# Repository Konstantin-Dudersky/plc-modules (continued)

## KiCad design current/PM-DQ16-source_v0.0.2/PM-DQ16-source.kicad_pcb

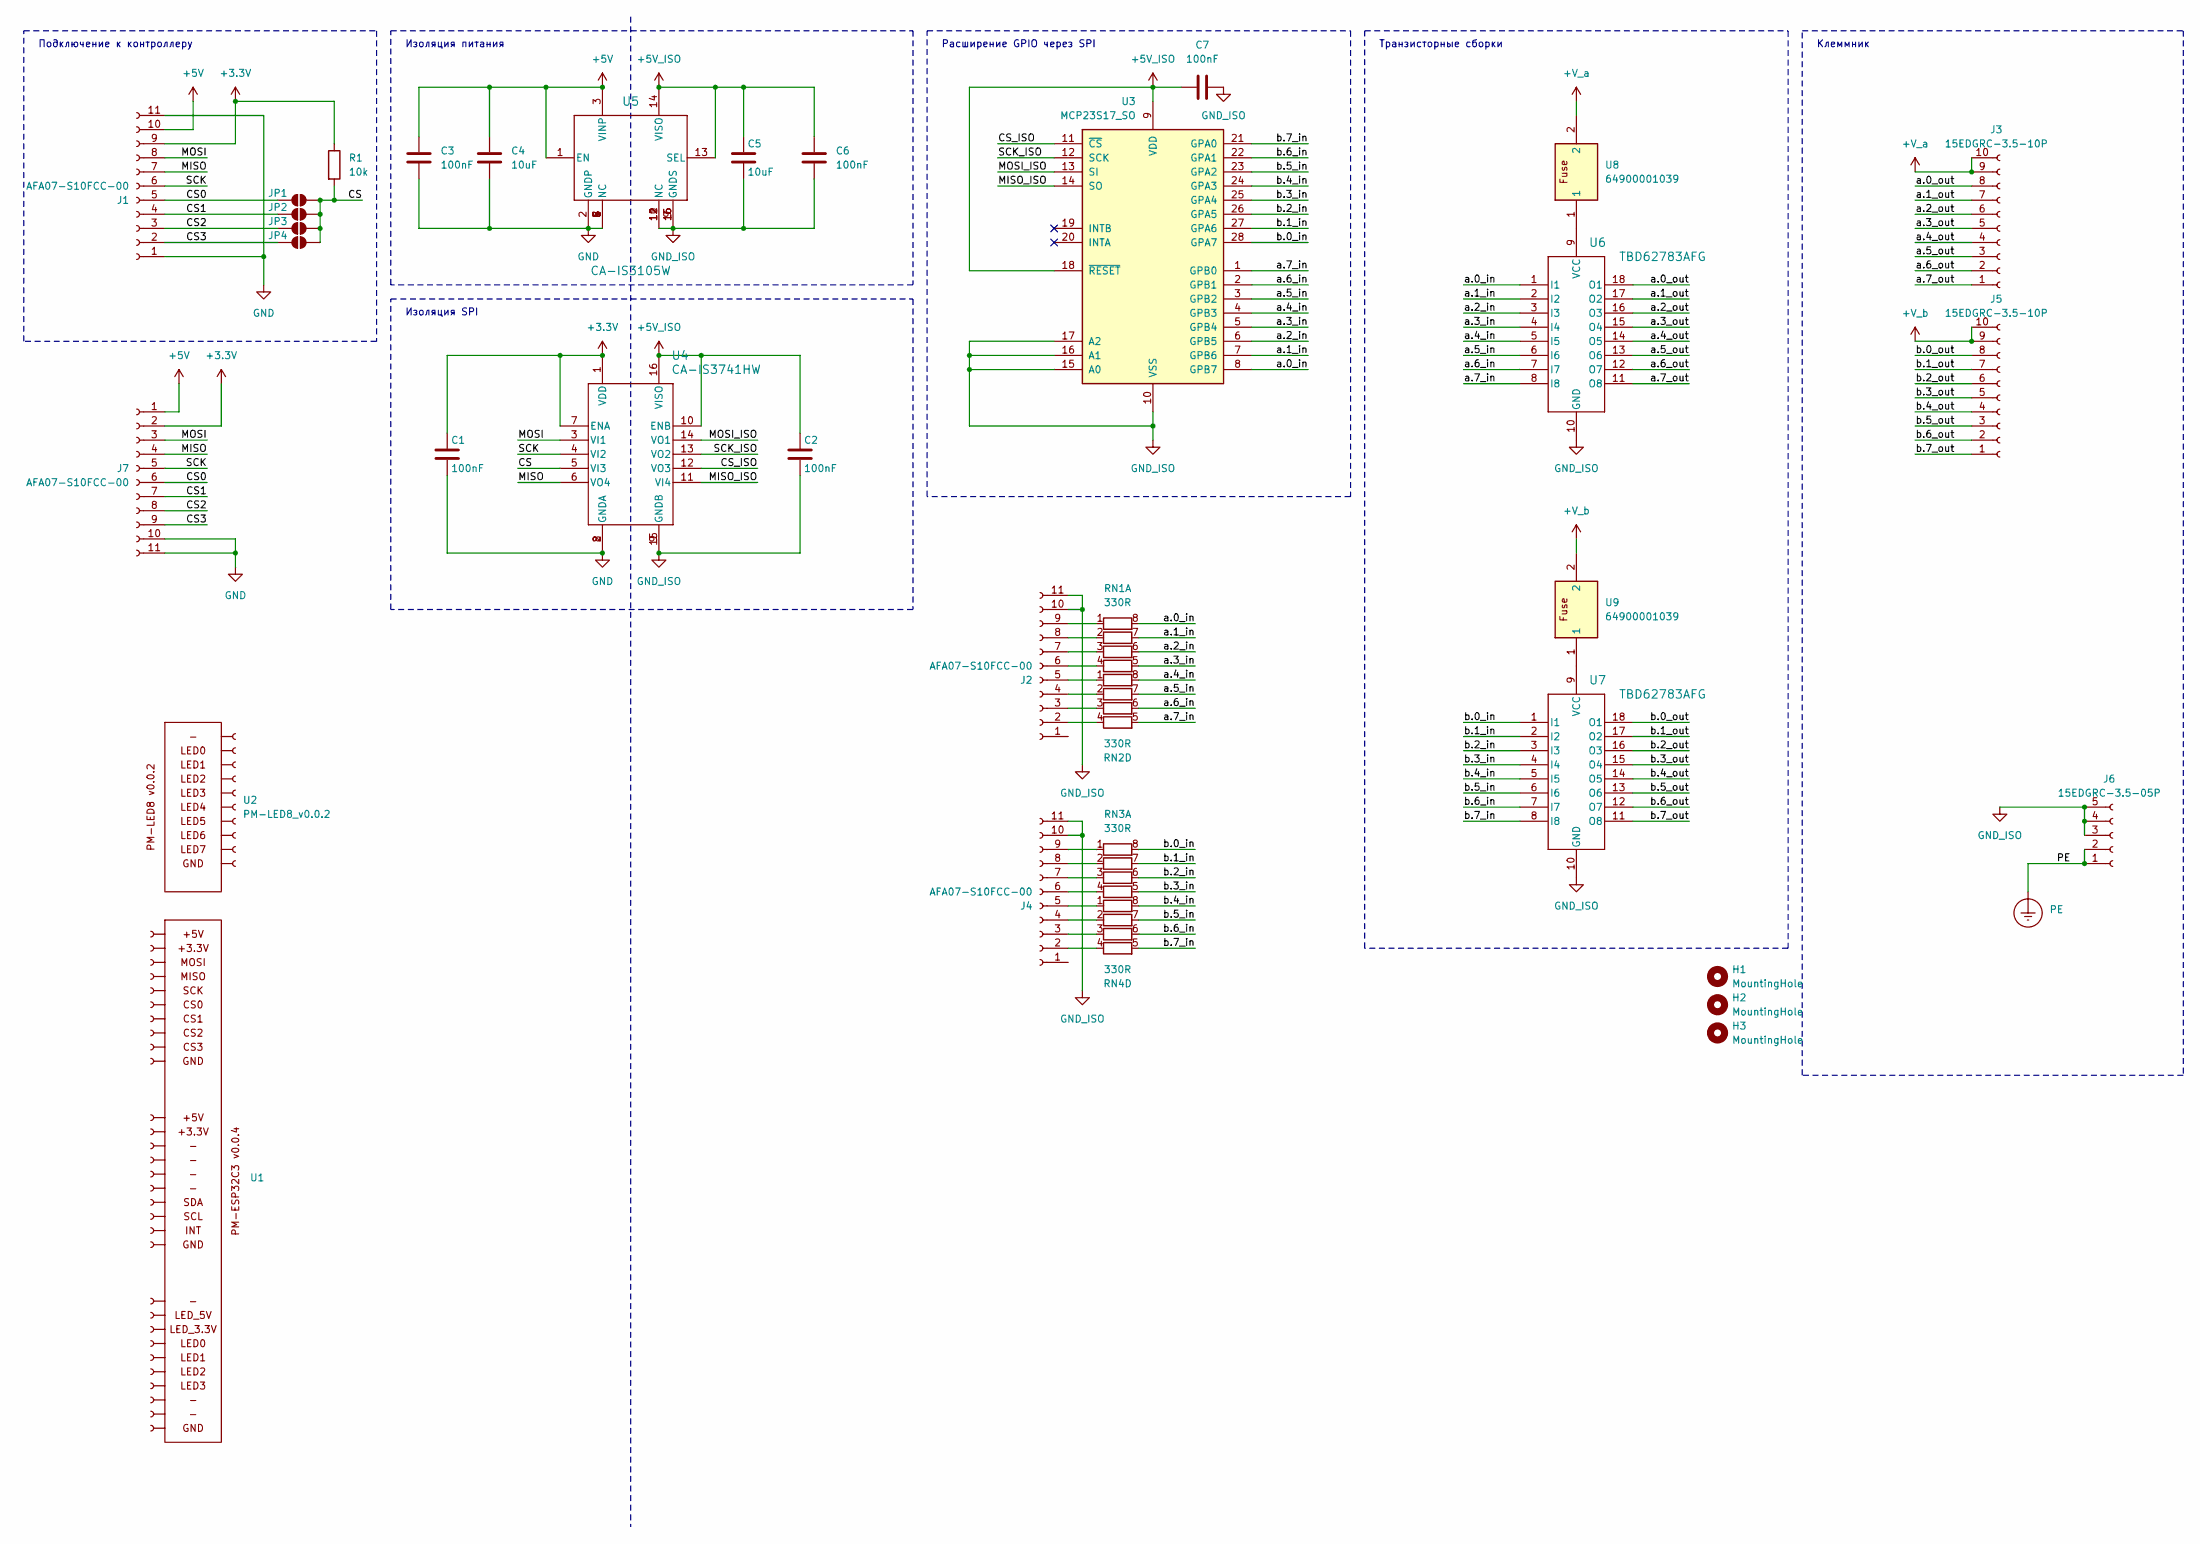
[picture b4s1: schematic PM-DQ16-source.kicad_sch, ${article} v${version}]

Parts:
C1, C2, C3, C6, C7: 100nF; C_0603_1608Metric; part_ipn C_100nF_16V_0603_MLCC-X7R
C4, C5: 10uF; C_0603_1608Metric; part_ipn C_10uF_16V_0603_MLCC-X5R
H1, H2, H3: MountingHole; MountingHole_3.2mm_M3
J1, J2, J4, J7: AFA07-S10FCC-00; CONN10_AFA07-S10_JUS; part_ipn AFA07-S10FCC-00
J3, J5: 15EDGRC-3.5-10P; part_ipn 15EDGRC-3.5-10P
J6: 15EDGRC-3.5-05P; part_ipn 15EDGRC-3.5-05P
JP1, JP2, JP3, JP4: SolderJumper_2_Open; SolderJumper-2_P1.3mm_Open_RoundedPad1.0x1.5mm
PE1: PE
R1: 10k; R_0603_1608Metric; part_ipn R_10k_0603_1%
RN1, RN2, RN3, RN4: 330R; R_Array_Convex_4x0603; part_ipn R_330R_0603x4_1%
U1: PM-ESP32C3_v0.0.4; part_ipn PM-ESP32C3_v0.0.4
U2: PM-LED8_v0.0.2; PM-LED_v0.0.2; part_ipn PM-LED8_v0.0.1
U3: MCP23S17_SO; SOIC-28W_7.5x17.9mm_P1.27mm; part_ipn MCP23S17-E/SO
U4: CA-IS3741HW; SOIC16-WBW_CLG-M; part_ipn CA-IS3741HW
U5: CA-IS3105W; SOIC16-WBW_CLG-M; part_ipn CA-IS3105W
U6, U7: TBD62783AFG; SOP18-P-375-1p27_TOS-M; part_ipn TBD62783AFG
U8, U9: 64900001039; Fuseholder; Manufacturer_Part_Number 64900001039; Mouser Part Number 576-64900001039

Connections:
+3.3V: C1.1, J1.9, J7.2, R1.1, U4.1 (VDD), U4.7 (ENA)
+5V: C3.1, C4.1, J1.10, J7.1, U5.1 (EN), U5.3 (VINP)
+5V_ISO: C2.1, C5.1, C6.1, C7.1, U3.9 (VDD), U3.18 (~RESET), U4.10 (ENB), U4.16 (VISO), U5.13 (SEL), U5.14 (VISO)
+V_a: J3.9, J3.10, U8.2
+V_b: J5.9, J5.10, U9.2
/CS: JP1.2 (B), JP2.2 (B), JP3.2 (B), JP4.2 (B), R1.2, U4.5 (VI3)
/CS0: J1.5, J7.6, JP1.1 (A)
/CS1: J1.4, J7.7, JP2.1 (A)
/CS2: J1.3, J7.8, JP3.1 (A)
/CS3: J1.2, J7.9, JP4.1 (A)
/CS_ISO: U3.11 (~CS), U4.12 (VO3)
/MISO: J1.7, J7.4, U4.6 (VO4)
/MISO_ISO: U3.14 (SO), U4.11 (VI4)
/MOSI: J1.8, J7.3, U4.3 (VI1)
/MOSI_ISO: U3.13 (SI), U4.14 (VO1)
/PE: J6.1, J6.2, PE1.1
/SCK: J1.6, J7.5, U4.4 (VI2)
/SCK_ISO: U3.12 (SCK), U4.13 (VO2)
/a.0_in: RN1.8 (R1.2), U3.8 (GPB7), U6.1 (I1)
/a.0_out: J3.8, U6.18 (O1)
/a.1_in: RN1.7 (R2.2), U3.7 (GPB6), U6.2 (I2)
/a.1_out: J3.7, U6.17 (O2)
/a.2_in: RN1.6 (R3.2), U3.6 (GPB5), U6.3 (I3)
/a.2_out: J3.6, U6.16 (O3)
/a.3_in: RN1.5 (R4.2), U3.5 (GPB4), U6.4 (I4)
/a.3_out: J3.5, U6.15 (O4)
/a.4_in: RN2.8 (R1.2), U3.4 (GPB3), U6.5 (I5)
/a.4_out: J3.4, U6.14 (O5)
/a.5_in: RN2.7 (R2.2), U3.3 (GPB2), U6.6 (I6)
/a.5_out: J3.3, U6.13 (O6)
/a.6_in: RN2.6 (R3.2), U3.2 (GPB1), U6.7 (I7)
/a.6_out: J3.2, U6.12 (O7)
/a.7_in: RN2.5 (R4.2), U3.1 (GPB0), U6.8 (I8)
/a.7_out: J3.1, U6.11 (O8)
/b.0_in: RN3.8 (R1.2), U3.28 (GPA7), U7.1 (I1)
/b.0_out: J5.8, U7.18 (O1)
/b.1_in: RN3.7 (R2.2), U3.27 (GPA6), U7.2 (I2)
/b.1_out: J5.7, U7.17 (O2)
/b.2_in: RN3.6 (R3.2), U3.26 (GPA5), U7.3 (I3)
/b.2_out: J5.6, U7.16 (O3)
/b.3_in: RN3.5 (R4.2), U3.25 (GPA4), U7.4 (I4)
/b.3_out: J5.5, U7.15 (O4)
/b.4_in: RN4.8 (R1.2), U3.24 (GPA3), U7.5 (I5)
/b.4_out: J5.4, U7.14 (O5)
/b.5_in: RN4.7 (R2.2), U3.23 (GPA2), U7.6 (I6)
/b.5_out: J5.3, U7.13 (O6)
/b.6_in: RN4.6 (R3.2), U3.22 (GPA1), U7.7 (I7)
/b.6_out: J5.2, U7.12 (O7)
/b.7_in: RN4.5 (R4.2), U3.21 (GPA0), U7.8 (I8)
/b.7_out: J5.1, U7.11 (O8)
GND: C1.2, C3.2, C4.2, J1.1, J1.11, J7.10, J7.11, U4.2 (GNDA), U4.8 (GNDA), U5.2 (GNDP), U5.4 (NC), U5.5 (NC), U5.6 (NC), U5.7 (NC), U5.8 (NC)
GND_ISO: C2.2, C5.2, C6.2, C7.2, J2.10, J2.11, J4.10, J4.11, J6.3, J6.4, J6.5, U3.10 (VSS), U3.15 (A0), U3.16 (A1), U3.17 (A2), U4.9 (GNDB), U4.15 (GNDB), U5.9 (GNDS), U5.10 (NC), U5.11 (NC), U5.12 (NC), U5.15 (GNDS), U5.16 (GNDS), U6.10 (GND), U7.10 (GND)
unnamed: J2.2, RN2.4 (R4.1)
unnamed: J2.3, RN2.3 (R3.1)
unnamed: J2.4, RN2.2 (R2.1)
unnamed: J2.5, RN2.1 (R1.1)
unnamed: J2.6, RN1.4 (R4.1)
unnamed: J2.7, RN1.3 (R3.1)
unnamed: J2.8, RN1.2 (R2.1)
unnamed: J2.9, RN1.1 (R1.1)
unnamed: J4.2, RN4.4 (R4.1)
unnamed: J4.3, RN4.3 (R3.1)
unnamed: J4.4, RN4.2 (R2.1)
unnamed: J4.5, RN4.1 (R1.1)
unnamed: J4.6, RN3.4 (R4.1)
unnamed: J4.7, RN3.3 (R3.1)
unnamed: J4.8, RN3.2 (R2.1)
unnamed: J4.9, RN3.1 (R1.1)
unnamed: U6.9 (VCC), U8.1
unnamed: U7.9 (VCC), U9.1

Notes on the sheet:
Изоляция SPI
Расширение GPIO через SPI
Подключение к контроллеру
Транзисторные сборки
Клеммник
Изоляция питания

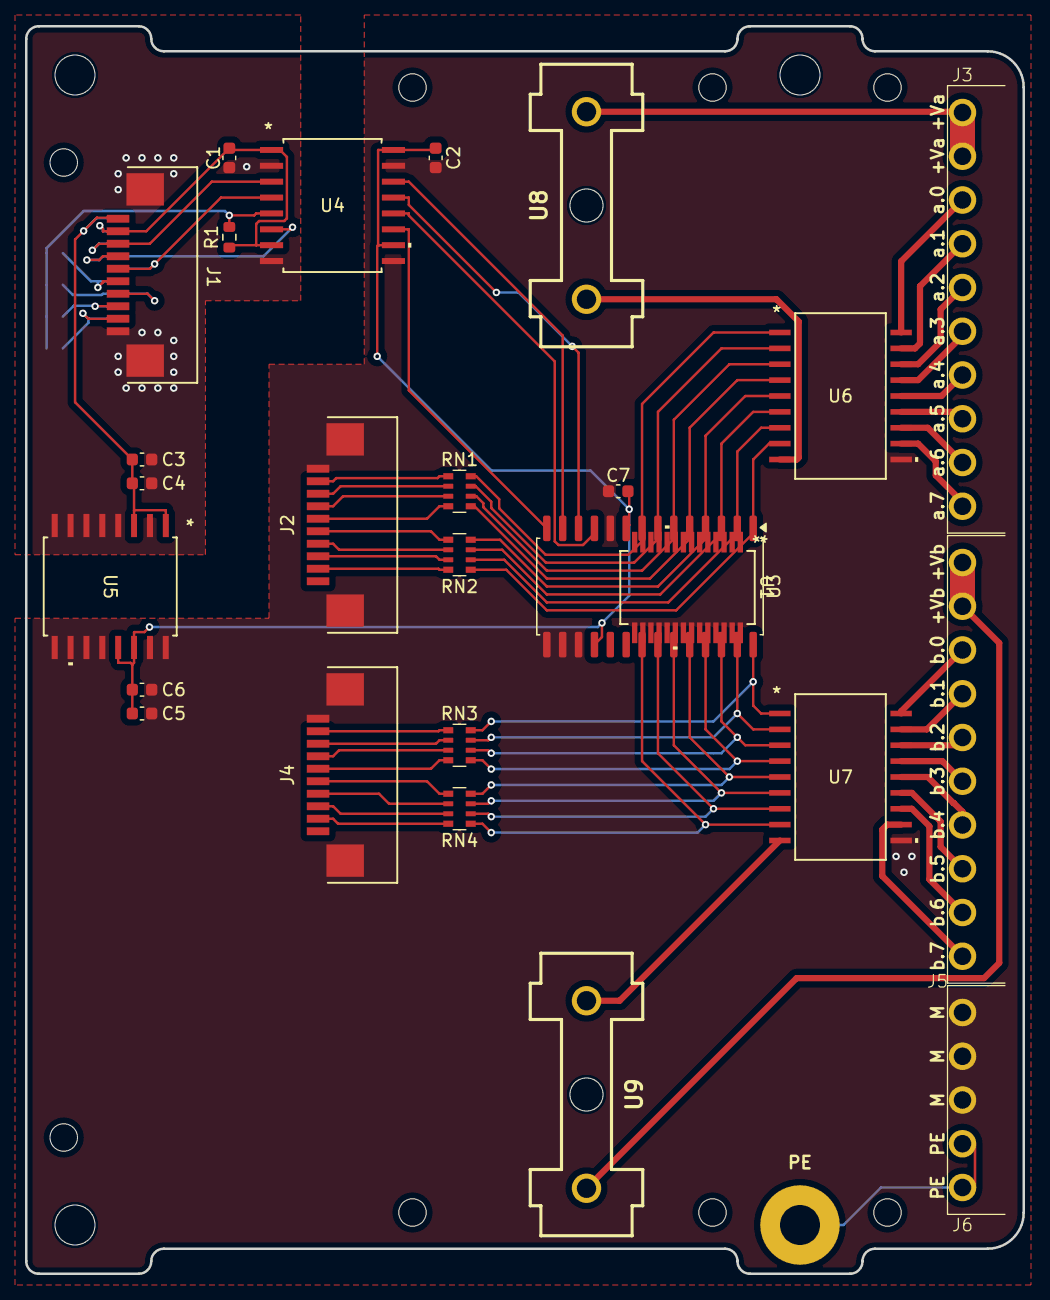
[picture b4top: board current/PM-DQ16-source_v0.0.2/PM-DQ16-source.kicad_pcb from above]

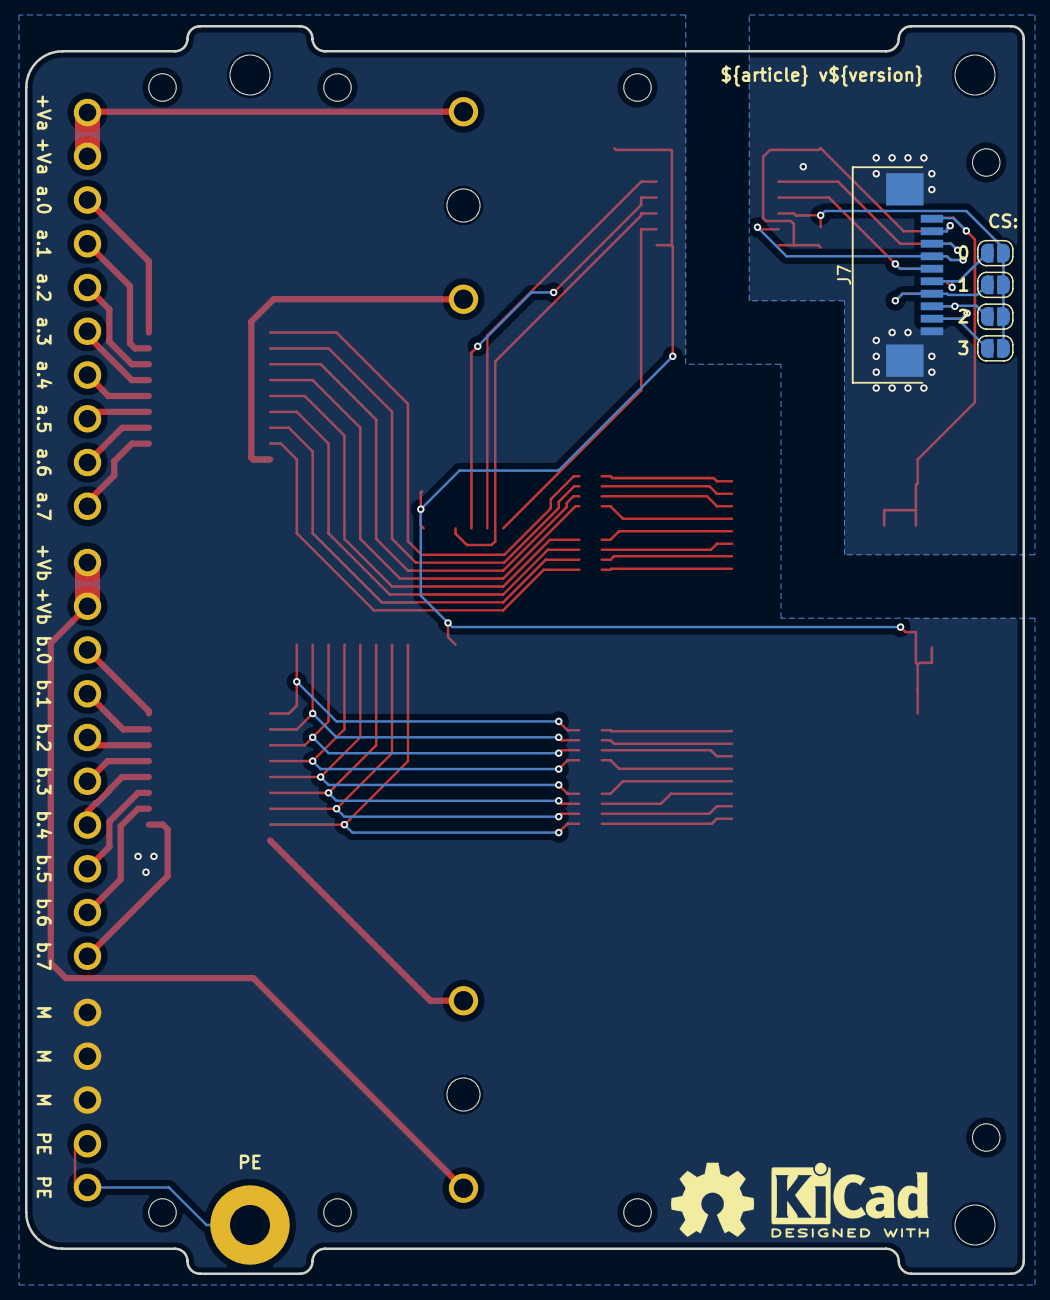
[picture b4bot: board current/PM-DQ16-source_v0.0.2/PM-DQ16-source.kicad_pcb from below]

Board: 2 copper layers, 79.8 x 99.8 mm, 39 parts (7 on the bottom side), 70 nets.

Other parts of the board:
U1#2: MCP23S17_SS; SSOP28_MC_MCH
kicad_logo: KiCad-Logo2_5mm_SilkScreen
oshw_logo: OSHW-Symbol_6.7x6mm_SilkScreen

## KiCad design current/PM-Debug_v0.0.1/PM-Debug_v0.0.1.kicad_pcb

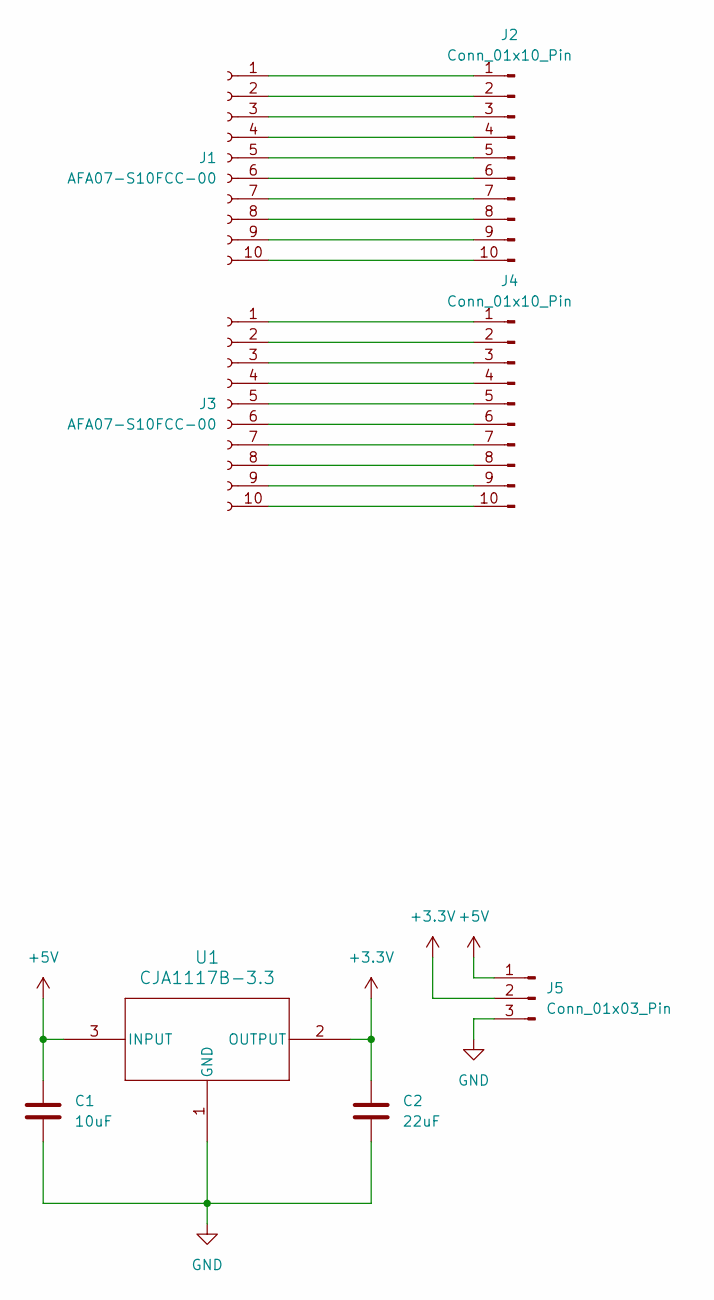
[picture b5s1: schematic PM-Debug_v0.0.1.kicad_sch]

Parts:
C1: 10uF; C_1206_3216Metric_Pad1.33x1.80mm_HandSolder; part_ipn C_10uF_16V_1206
C2: 22uF; C_1206_3216Metric_Pad1.33x1.80mm_HandSolder; part_ipn C_22uF_16V_1206
J1: AFA07-S10FCC-00; CONN10_AFA07-S10_JUS; part_ipn AFA07-S10FCC-00
J2, J4: Conn_01x10_Pin; PinHeader_1x10_P2.54mm_Vertical
J3: AFA07-S10FCC-00; CONN10_AFA07-S10_JUS
J5: Conn_01x03_Pin; PinHeader_1x03_P2.54mm_Vertical
U1: CJA1117B-3.3; SOT-89-3; part_ipn CJA1117B-3.3

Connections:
+3.3V: C2.1, J5.2, U1.2 (OUTPUT)
+5V: C1.1, J5.1, U1.3 (INPUT)
GND: C1.2, C2.2, J5.3, U1.1 (GND)
unnamed: J1.1, J2.1
unnamed: J1.2, J2.2
unnamed: J1.3, J2.3
unnamed: J1.4, J2.4
unnamed: J1.5, J2.5
unnamed: J1.6, J2.6
unnamed: J1.7, J2.7
unnamed: J1.8, J2.8
unnamed: J1.9, J2.9
unnamed: J1.10, J2.10
unnamed: J3.1, J4.1
unnamed: J3.2, J4.2
unnamed: J3.3, J4.3
unnamed: J3.4, J4.4
unnamed: J3.5, J4.5
unnamed: J3.6, J4.6
unnamed: J3.7, J4.7
unnamed: J3.8, J4.8
unnamed: J3.9, J4.9
unnamed: J3.10, J4.10

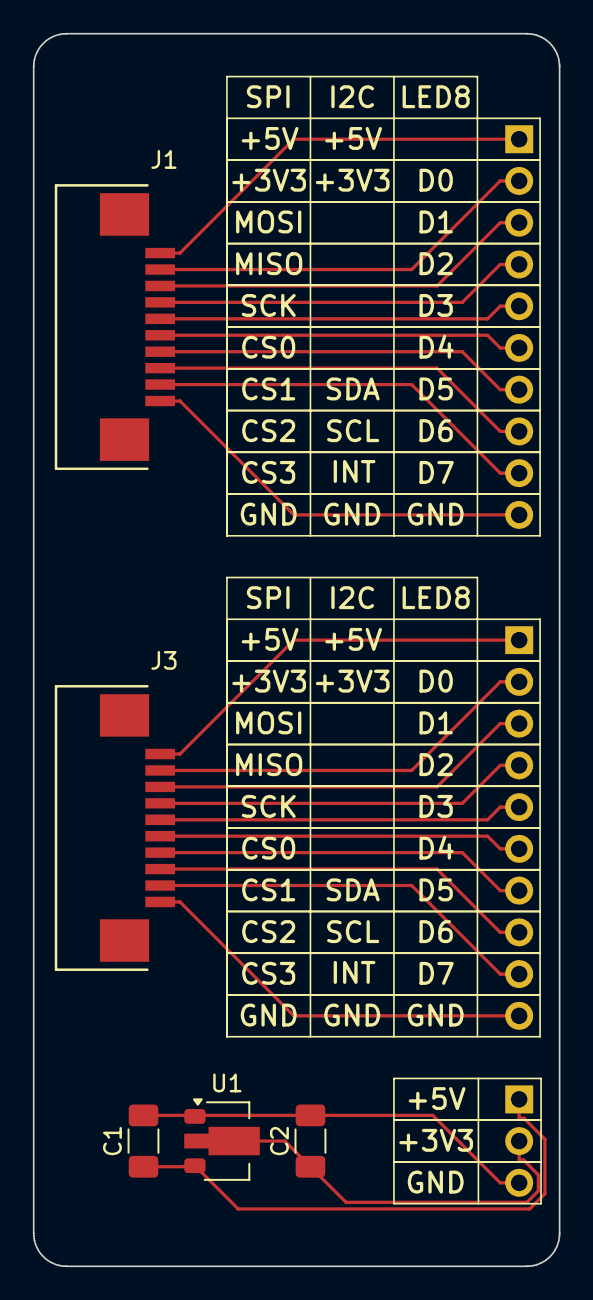
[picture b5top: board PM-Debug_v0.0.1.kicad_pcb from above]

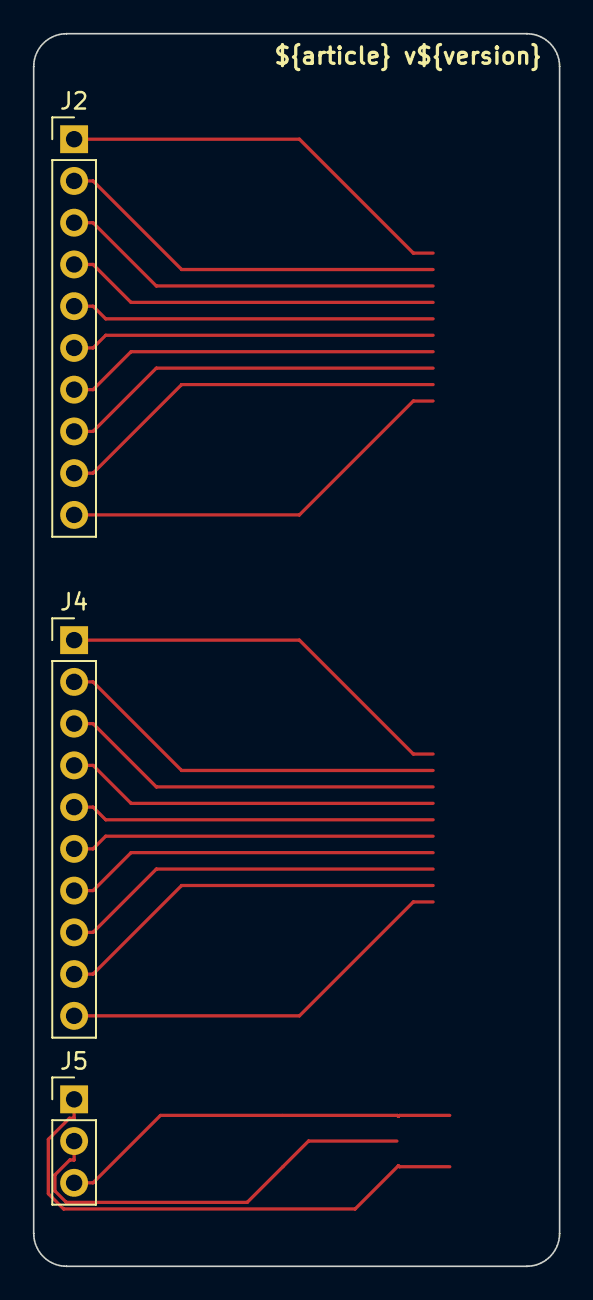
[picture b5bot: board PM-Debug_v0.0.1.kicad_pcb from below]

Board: 2 copper layers, 32.0 x 75.0 mm, 8 parts (3 on the bottom side), 23 nets.

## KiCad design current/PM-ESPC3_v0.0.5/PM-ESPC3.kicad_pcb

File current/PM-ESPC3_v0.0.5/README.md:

v0.0.5:

- увеличил размеры платы на 0.1
- конденсаторы 10uF в типоразмере 0805
- тестовые пины для UART
- удалил 5В от USB

TODO:
- возможно отказаться от MicroUSB-разъема, сделать свой 4-пиновый

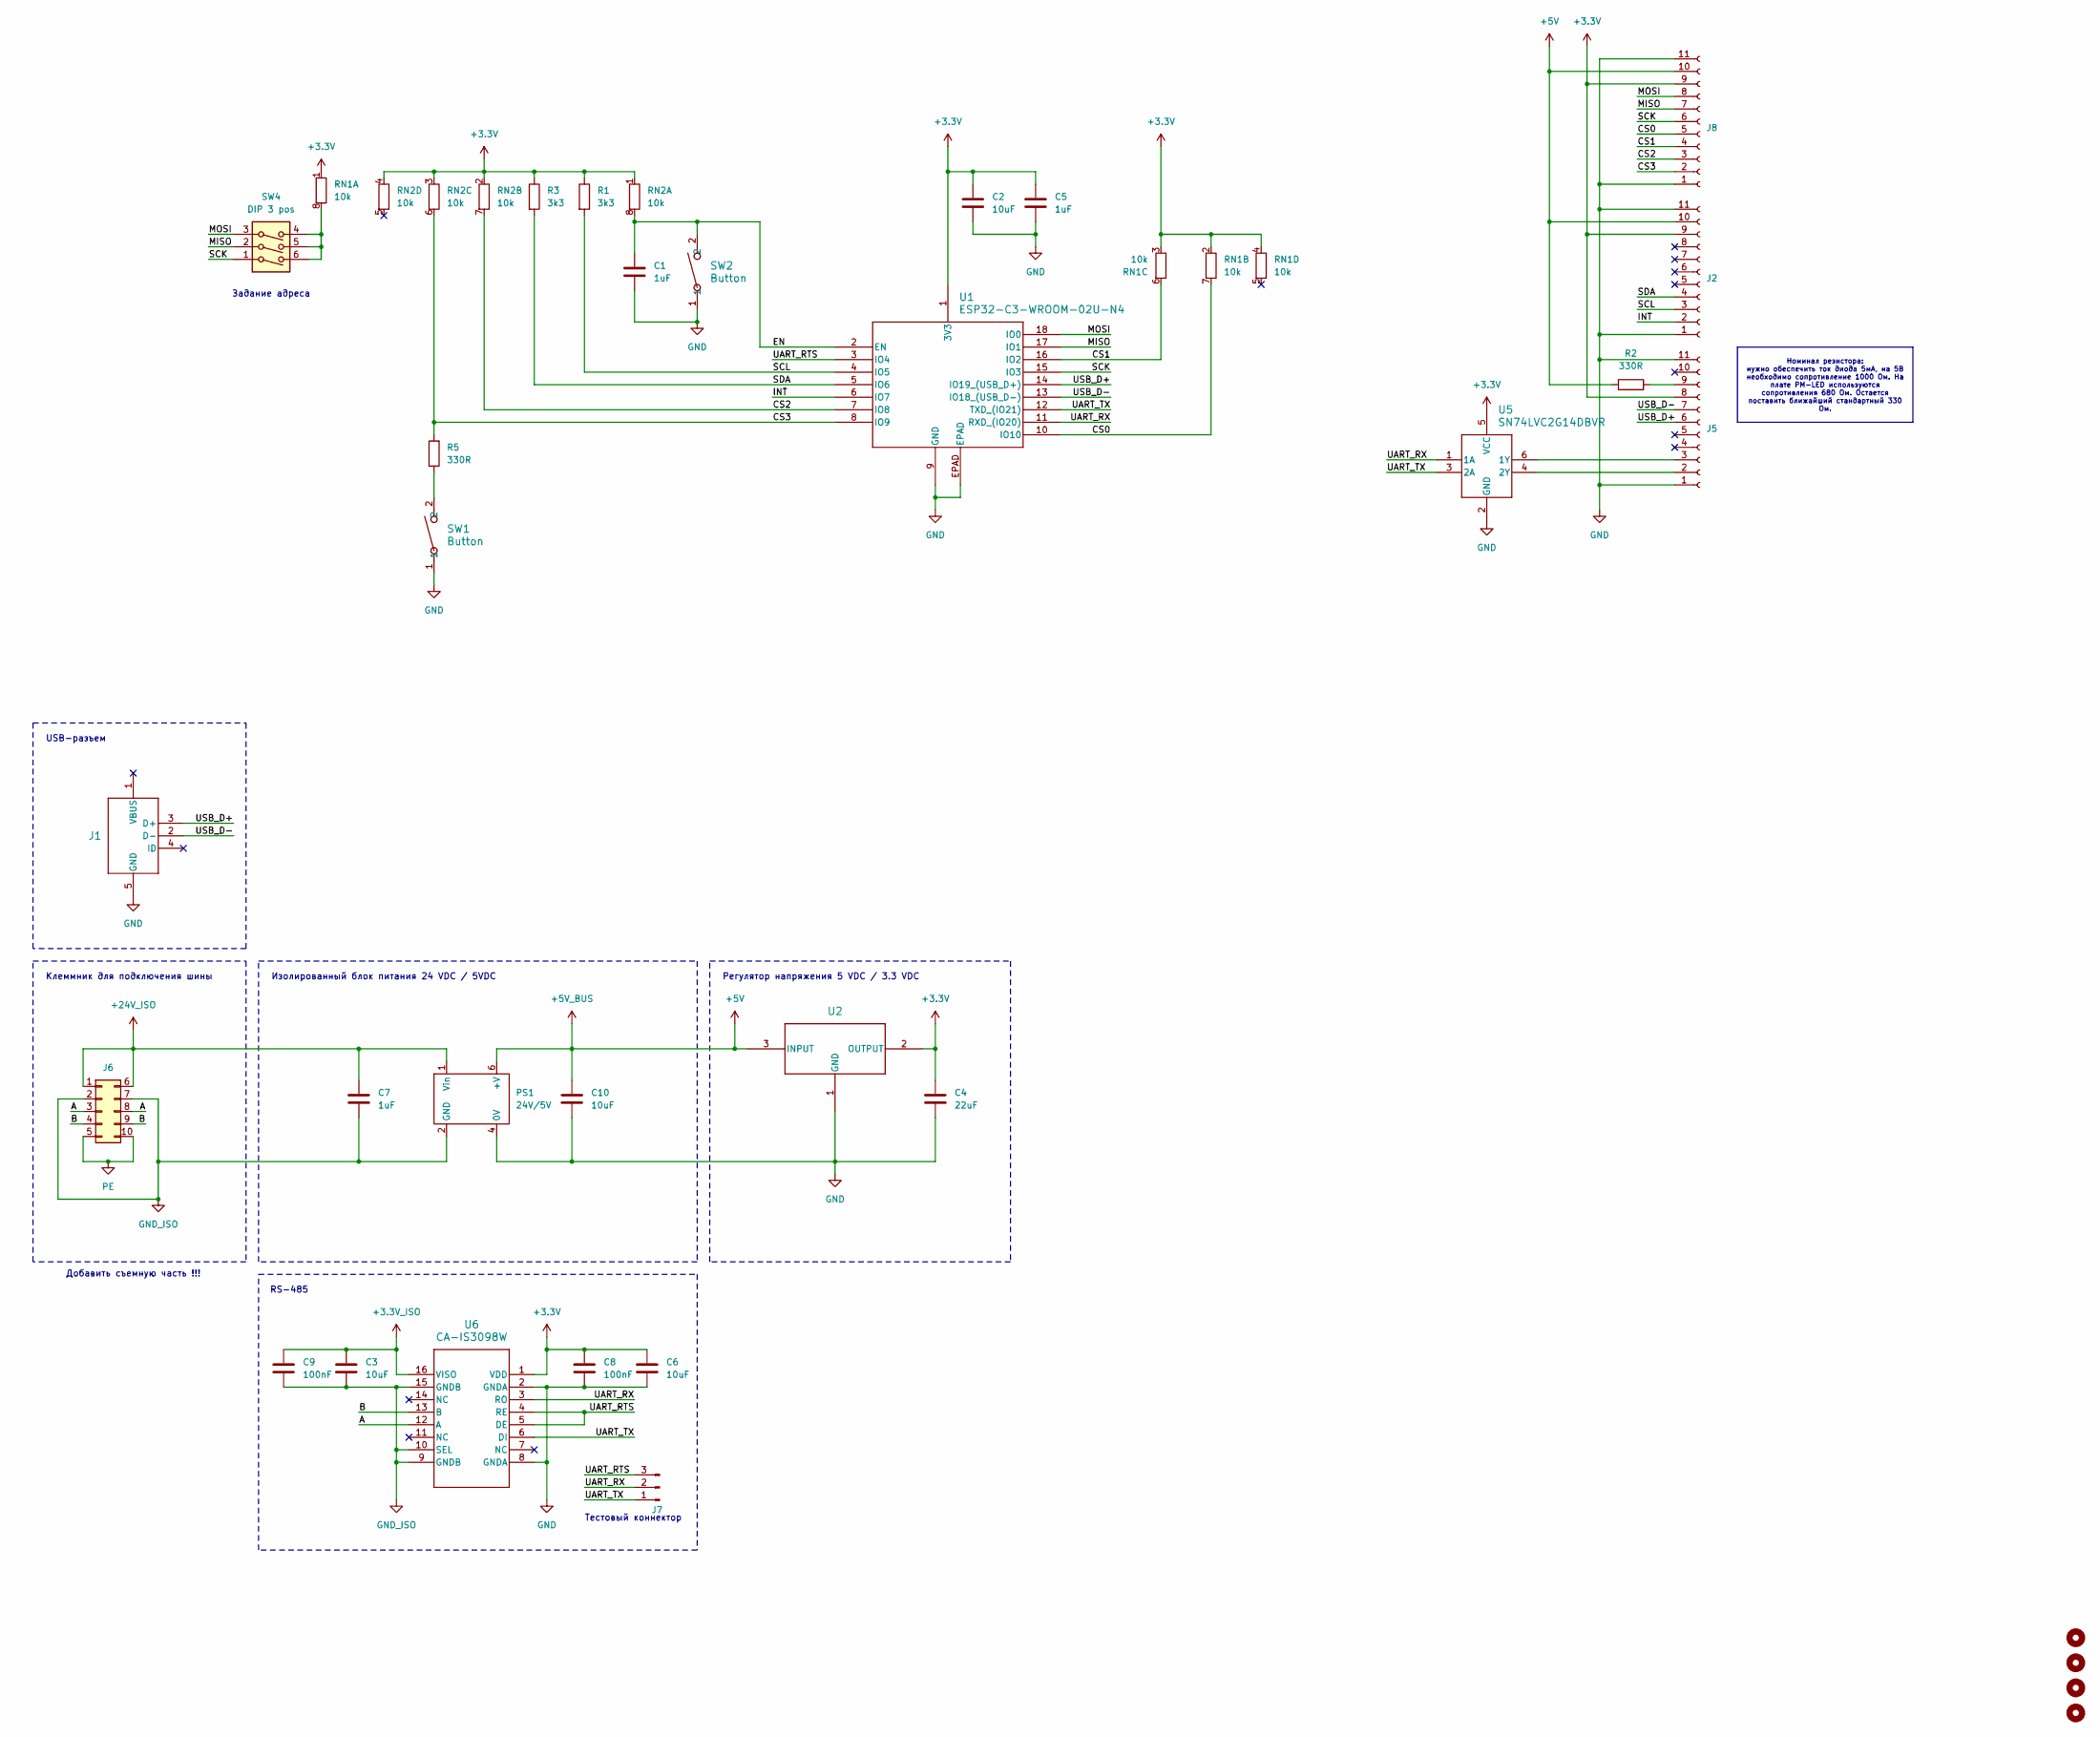
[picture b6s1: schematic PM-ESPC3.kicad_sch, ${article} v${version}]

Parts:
C1, C5: 1uF; C_0603_1608Metric; part_ipn C_1uF_16V_0603_MLCC-X7R
C2, C3, C6, C10: 10uF; C_0805_2012Metric; part_ipn C_10uF_16V_0805_MLCC-X5R
C4: 22uF; C_0603_1608Metric; part_ipn C_22uF_16V_0603_MLCC-X5R
C7: 1uF; C_0603_1608Metric; part_ipn C_1uF_50V_0603_MLCC-X7R
C8, C9: 100nF; C_0603_1608Metric; part_ipn C_100nF_16V_0603_MLCC-X7R
H1, H2, H3, H4: MountingHole_M2
J1: U254-051T-4BH83-S1S; CONN5_H83-S1S_XKB; part_ipn U254-051T-4BH83-S1S
J2, J5, J8: AFA07-S10FCC-00; CONN10_AFA07-S10_JUS; part_ipn AFA07-S10FCC-00
J6: 15EDGRHC-THR-3.5-10P; part_ipn 15EDGRHC-THR-3.5-10P
J7: PinHeader_01x03_P1.00_THT_straight; PinHeader_1x03_P1.00mm_Vertical; part_ipn PinHeader_01x03_P2.54_THT_straight
PS1: 24V/5V; B2405LS-1WR3; part_ipn B2405LS-1WR3
R1, R3: 3k3; R_0603_1608Metric; part_ipn R_3k3_0603_1%
R2, R5: 330R; R_0603_1608Metric; part_ipn R_330R_0603_1%
RN1, RN2: 10k; R_Array_Convex_4x0603; part_ipn R_10k_0603x4_1%
SW1, SW2: Button; SW_TS-1088_XNP-M; part_ipn TS-1088-AR02016
SW4: DIP 3 pos; DA03BLP; part_ipn DA-03BLP
U1: ESP32-C3-WROOM-02U-N4; ESP32-C3-WROOM-02U_EXP; part_ipn ESP32-C3-WROOM-02U-N4
U2: CJA1117B-3.3; SOT-89-3; part_ipn CJA1117B-3.3
U5: SN74LVC2G14DBVR; DBV6-M; part_ipn SN74LVC2G14DBVR
U6: CA-IS3098W; SOIC16-WBW_CLG; part_ipn CA-IS3098W

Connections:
+3.3V: C2.1, C4.1, C5.1, C6.1, C8.1, J2.9, J5.8, J8.9, R1.1, R3.1, RN1.1 (R1.1), RN1.2 (R2.1), RN1.3 (R3.1), RN1.4 (R4.1), RN2.1 (R1.1), RN2.2 (R2.1), RN2.3 (R3.1), RN2.4 (R4.1), U1.1 (3V3), U2.2 (OUTPUT), U5.5 (VCC), U6.1 (VDD)
+3.3V_ISO: C3.1, C9.1, U6.16 (VISO)
+5V: C10.1, J2.10, J8.10, PS1.6 (+V), R2.1, U2.3 (INPUT)
+24V_ISO: C7.1, J6.1, J6.6 (Pin_2), PS1.1 (Vin)
/A: J6.3, J6.8 (Pin_6), U6.12 (A)
/B: J6.4, J6.9 (Pin_8), U6.13 (B)
/CS0: J8.5, RN1.7 (R2.2), U1.10 (IO10)
/CS1: J8.4, RN1.6 (R3.2), U1.16 (IO2)
/CS2: J8.3, RN2.7 (R2.2), U1.7 (IO8)
/CS3: J8.2, R5.2, RN2.6 (R3.2), U1.8 (IO9)
/EN: C1.1, RN2.8 (R1.2), SW2.2, U1.2 (EN)
/INT: J2.2, U1.6 (IO7)
/MISO: J8.7, SW4.2, U1.17 (IO1)
/MOSI: J8.8, SW4.3, U1.18 (IO0)
/SCK: J8.6, SW4.1, U1.15 (IO3)
/SCL: J2.3, R1.2, U1.4 (IO5)
/SDA: J2.4, R3.2, U1.5 (IO6)
/UART_RTS: J7.3, U1.3 (IO4), U6.4 (RE), U6.5 (DE)
/UART_RX: J7.2, U1.11 (RXD_(IO20)), U5.1 (1A), U6.3 (RO)
/UART_TX: J7.1, U1.12 (TXD_(IO21)), U5.3 (2A), U6.6 (DI)
/USB_D+: J1.3 (D+), J5.6, U1.14 (IO19_(USB_D+))
/USB_D-: J1.2 (D-), J5.7, U1.13 (IO18_(USB_D-))
GND: C1.2, C2.2, C4.2, C5.2, C6.2, C8.2, C10.2, J1.5 (GND), J2.1, J2.11, J5.1, J5.11, J8.1, J8.11, PS1.4 (0V), SW1.1, SW2.1, U1.9 (GND), U1.EPAD, U2.1 (GND), U5.2 (GND), U6.2 (GNDA), U6.8 (GNDA)
GND_ISO: C3.2, C7.2, C9.2, J6.2 (Pin_3), J6.7 (Pin_4), PS1.2 (GND), U6.9 (GNDB), U6.10 (SEL), U6.15 (GNDB)
unnamed: J5.2, U5.4 (2Y)
unnamed: J5.3, U5.6 (1Y)
unnamed: J5.9, R2.2
unnamed: R5.1, SW1.2
unnamed: RN1.8 (R1.2), SW4.4, SW4.5, SW4.6
PE: J6.5 (Pin_9), J6.10

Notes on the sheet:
Номинал резистора: нужно обеспечить ток диода 5мА, на 5В необходимо сопротивление 1000 Ом. На плате PM-LED используются сопротивления 680 Ом. Остается поставить ближайший стандартный 330 Ом.
USB-разъем
Задание адреса
RS-485
Регулятор напряжения 5 VDC / 3.3 VDC
Добавить съемную часть !!!
Изолированный блок питания 24 VDC / 5VDC
Тестовый коннектор
Клеммник для подключения шины

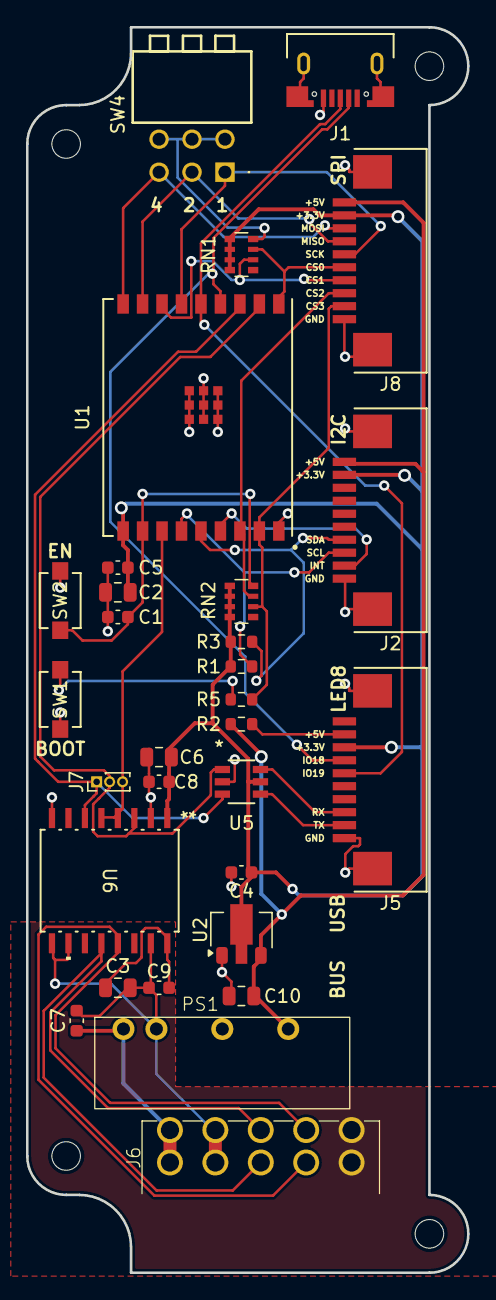
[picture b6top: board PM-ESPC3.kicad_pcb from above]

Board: 2 copper layers, 34.0 x 96.0 mm, 34 parts (0 on the bottom side), 30 nets.
